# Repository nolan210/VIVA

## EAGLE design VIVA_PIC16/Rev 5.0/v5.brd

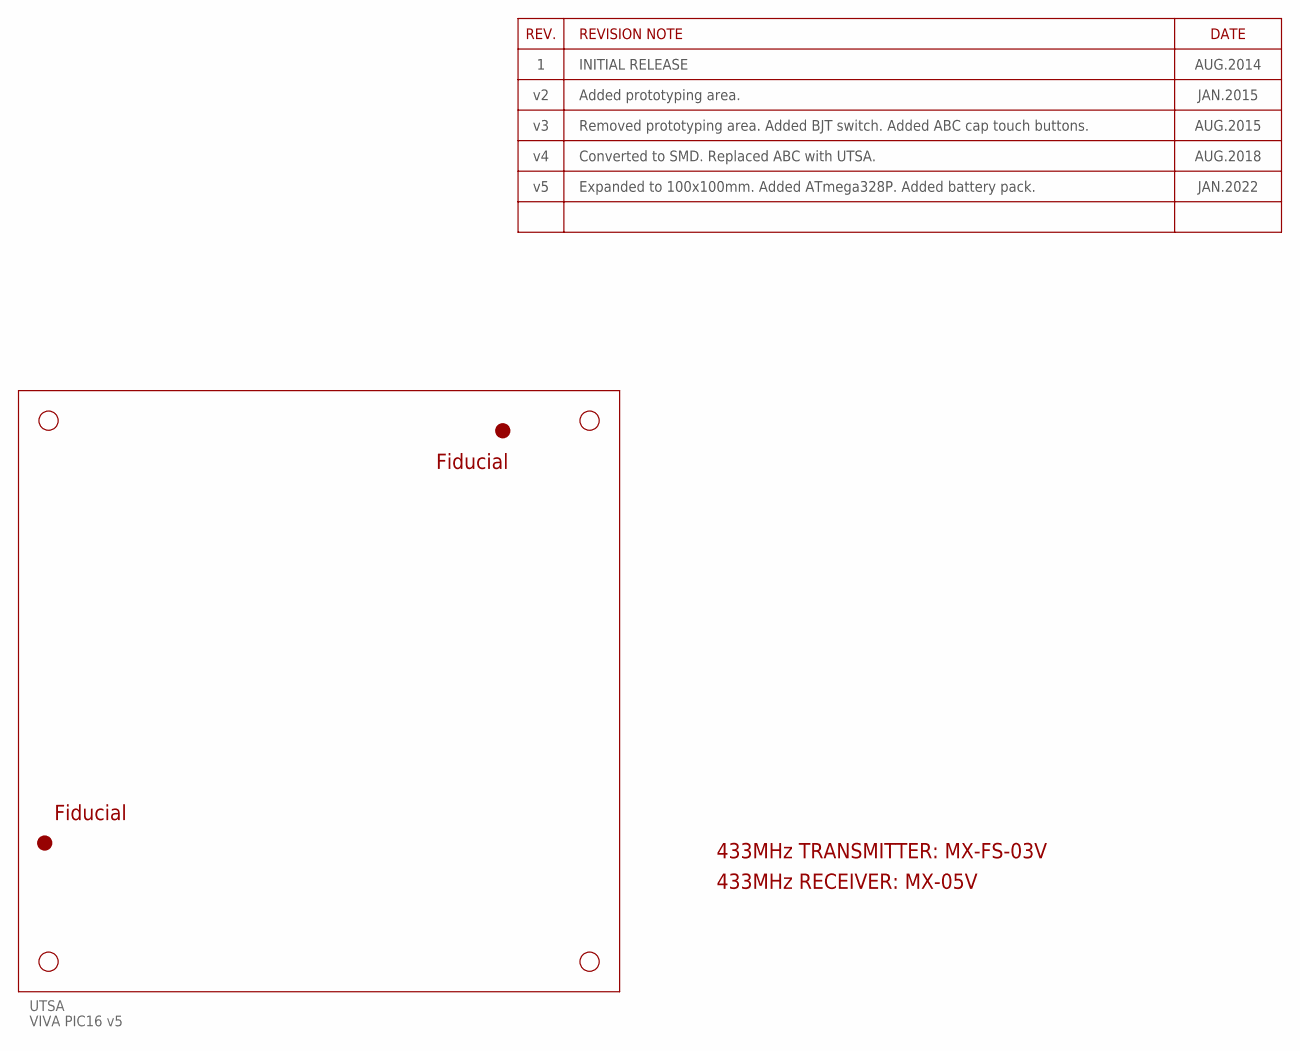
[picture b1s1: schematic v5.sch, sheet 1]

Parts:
FIDUCIAL1, FIDUCIAL2: FIDUCIAL
UTSA: VIVA PIC16 v5; PCB_100X100

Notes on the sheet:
Fiducial
433MHz TRANSMITTER: MX-FS-03V
433MHz RECEIVER: MX-05V

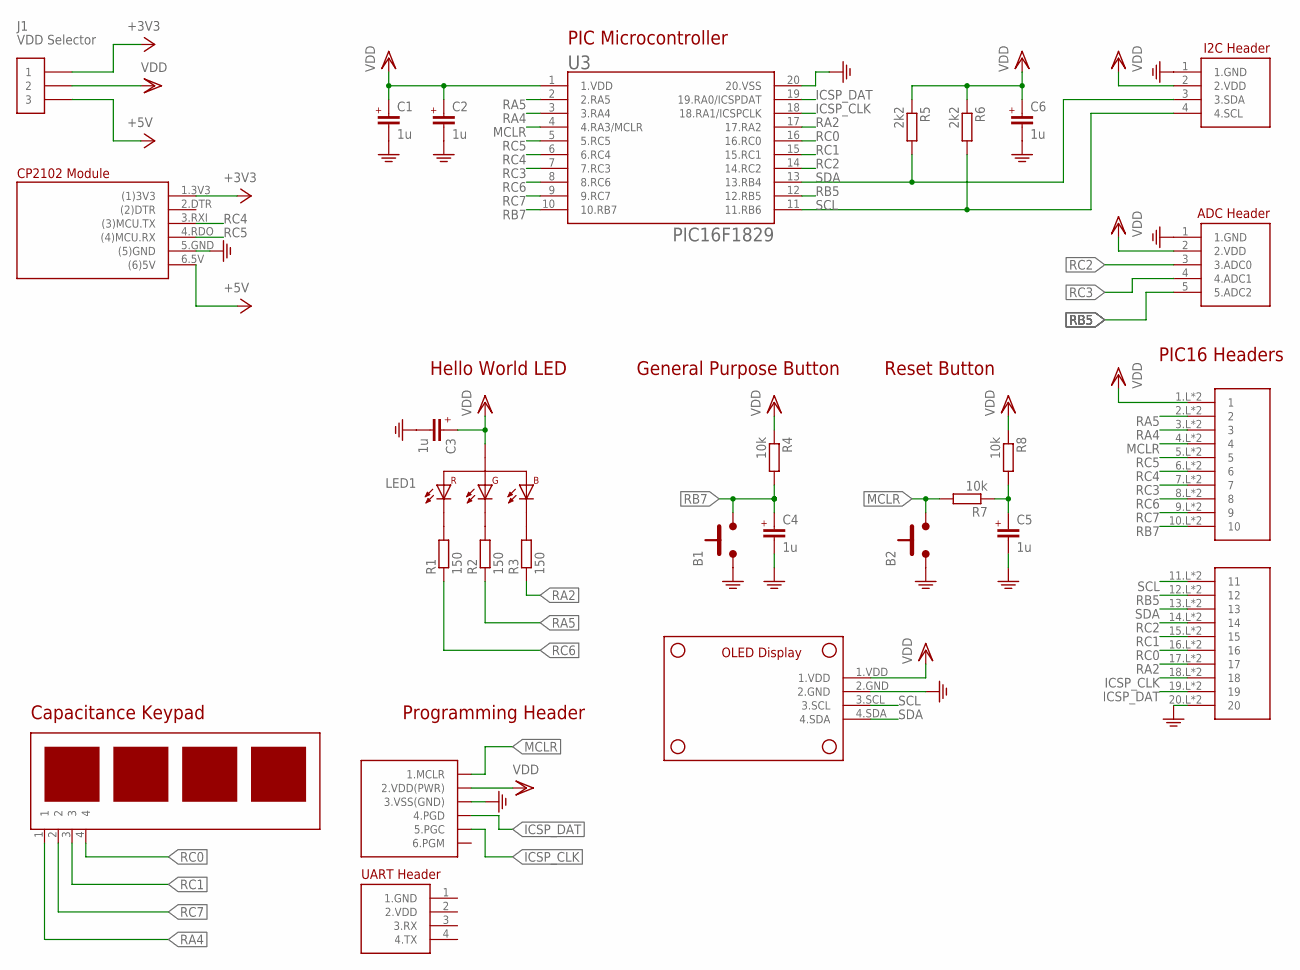
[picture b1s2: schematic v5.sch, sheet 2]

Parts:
B1, B2: PUSHBUTTON6X6MM; 6X6MM
C1, C2, C3, C4, C5, C6: 1u; C0805
J1: VDD Selector; PINS_3
J4: PICKIT3
J5: VIVA-HEADER-ADC-PIC16
LED1: LED_RGBLTST-C19FD1WT; 0805_RGB
R1, R2, R3: 150; R0805
R4, R7, R8: 10k; R0805
R5, R6: 2k2; R0805
U1: VIVA_UTSA-KEYPADV5; VIVA_UTSA-KEYPAD-V5
U2: VIVA_USB-TTL; VIVA_USB_TTL_SUBTEXT
U3: PIC16F1829; SOP20-NEW
U4: VIVA-HEADER-I2C-RA
U5: VIVA_PIC16BOARD; VIVA_PIC16
U$2: VIVA-HEADER-UART-XS; PINS_4
U$3: VIVA_OLED; VIVA_OLED-I2C

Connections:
+3V3: J1.1, U2.1.3V3 ((1)3V3); also elsewhere on the board
+5V: J1.3, U2.6.5V ((6)5V); also elsewhere on the board
GND: B1.1.A (1), B1.2.A (1), B2.1.A (1), B2.2.A (1), C1.1 (-), C2.1 (-), C3.1 (-), C4.1 (-), C5.1 (-), C6.1 (-), J4.3 (3.VSS(GND)), J5.1 (1.GND), U2.5.GND ((5)GND), U3.20 (20.VSS), U4.1 (1.GND), U5.20.L (20), U5.20.R (20), U$3.2.GND; also elsewhere on the board
ICSP_CLK: J4.5 (5.PGC), U3.18 (18.RA1/ICSPCLK), U5.18.L (18), U5.18.R (18)
ICSP_DAT: J4.4 (4.PGD), U3.19 (19.RA0/ICSPDAT), U5.19.L (19), U5.19.R (19)
MCLR: B2.3.B (2), B2.4.B (2), J4.1 (1.MCLR), R7.2, U3.4 (4.RA3/MCLR), U5.4.L (4), U5.4.R (4)
MCLR_CAP: C5.2 (+), R7.1, R8.2
unnamed: LED1.2 (1.R-), R1.2
unnamed: LED1.3 (2.G-), R2.2
unnamed: LED1.1 (4.B-), R3.2
RA2: R3.1, U3.17 (17.RA2), U5.17.L (17), U5.17.R (17)
RA4: U1.1, U3.3 (3.RA4), U5.3.L (3), U5.3.R (3)
RA5: R2.1, U3.2 (2.RA5), U5.2.L (2), U5.2.R (2)
RB5: J5.5 (5.ADC2), U3.12 (12.RB5), U5.12.L (12), U5.12.R (12)
RB7: B1.3.B (2), B1.4.B (2), C4.2 (+), R4.2, U3.10 (10.RB7), U5.10.L (10), U5.10.R (10)
RC0: U1.4, U3.16 (16.RC0), U5.16.L (16), U5.16.R (16)
RC1: U1.3, U3.15 (15.RC1), U5.15.L (15), U5.15.R (15)
RC2: J5.3 (3.ADC0), U3.14 (14.RC2), U5.14.L (14), U5.14.R (14)
RC3: J5.4 (4.ADC1), U3.7 (7.RC3), U5.7.L (7), U5.7.R (7)
RC4: U2.3.RXI ((3)MCU.TX), U3.6 (6.RC4), U5.6.L (6), U5.6.R (6)
RC5: U2.4.RDO ((4)MCU.RX), U3.5 (5.RC5), U5.5.L (5), U5.5.R (5)
RC6: R1.1, U3.8 (8.RC6), U5.8.L (8), U5.8.R (8)
RC7: U1.2, U3.9 (9.RC7), U5.9.L (9), U5.9.R (9)
SCL: R6.2, U3.11 (11.RB6), U4.4 (4.SCL), U5.11.L (11), U5.11.R (11), U$3.3.SCL; also elsewhere on the board
SDA: R5.2, U3.13 (13.RB4), U4.3 (3.SDA), U5.13.L (13), U5.13.R (13), U$3.4.SDA; also elsewhere on the board
VDD: C1.2 (+), C2.2 (+), C3.2 (+), C6.2 (+), J1.2, J4.2 (2.VDD(PWR)), J5.2 (2.VDD), LED1.4 (3.+), R4.1, R5.1, R6.1, R8.1, U3.1 (1.VDD), U4.2 (2.VDD), U5.1.L (1), U5.1.R (1), U$3.1.VDD; also elsewhere on the board

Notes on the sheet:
General Purpose Button
Hello World LED
PIC Microcontroller
Capacitance Keypad
Reset Button
Programming Header
PIC16 Headers

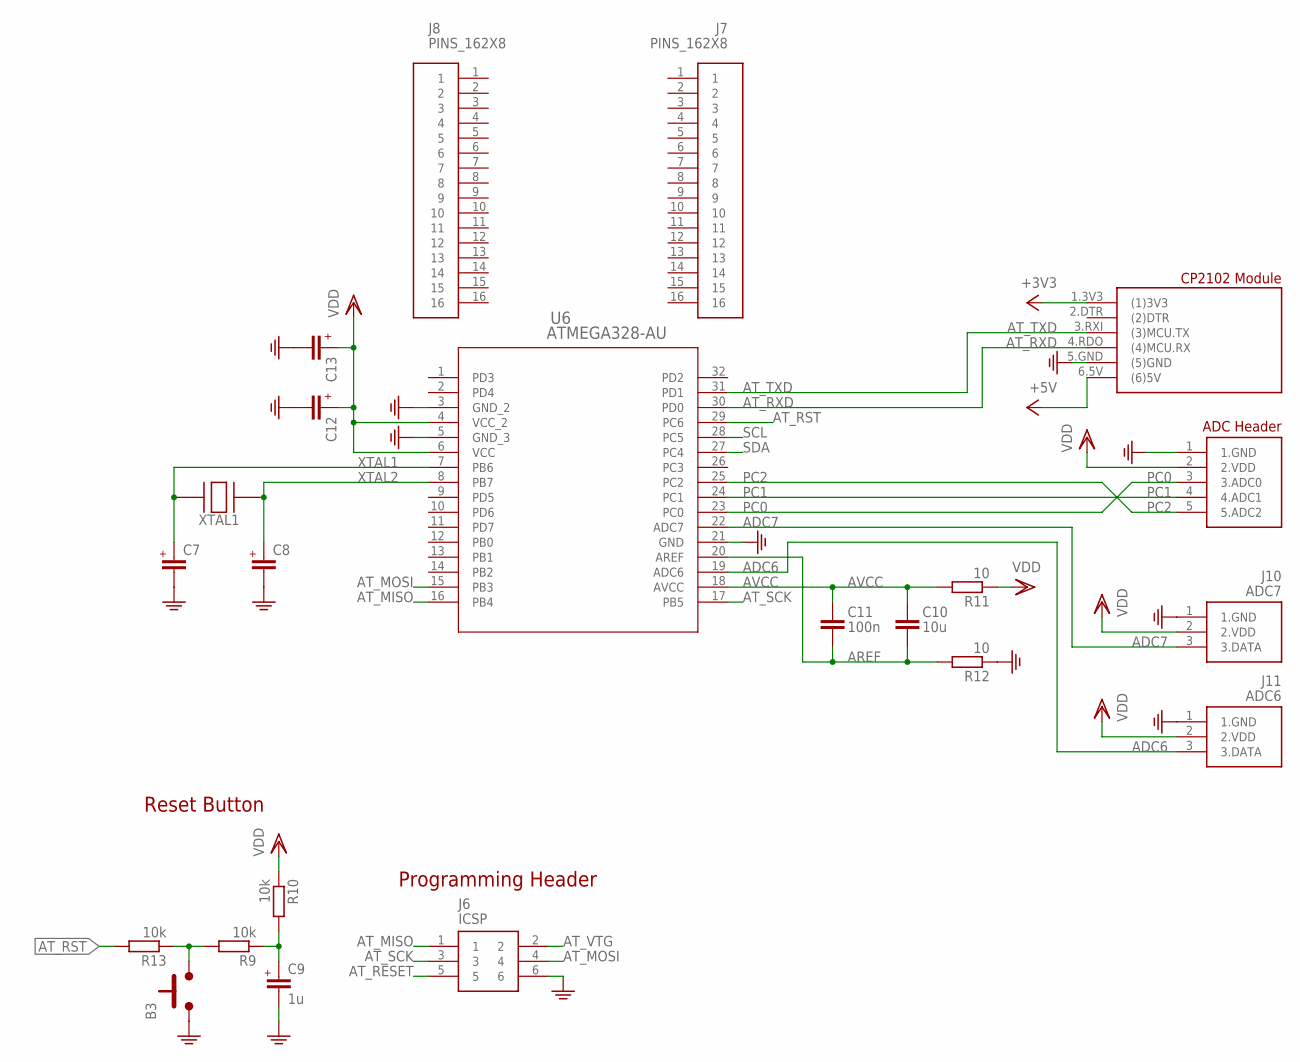
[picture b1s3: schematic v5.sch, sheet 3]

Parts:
B3: PUSHBUTTON6X6MM; 6X6MM
C7, C8, C12, C13: C0805
C9: 1u; C0805
C10: 10u; C0805
C11: 100n; C0805
J6: ICSP; PINS_6-2X3
J7, J8: PINS_162X8; PINS16_2X8
J9: VIVA-HEADER-ADC-PIC16
J10: ADC7; VIVA-HEADER-GPIO-RA-1
J11: ADC6; VIVA-HEADER-GPIO-RA-1
R9, R10, R13: 10k; R0805
R11, R12: 10; R0805
U6: ATMEGA328-AU; 32A_ATM
U7: VIVA_USB-TTL; VIVA_USB_TTL_SUBTEXT
XTAL1: CRYSTAL-SMD; HC49S-SMD

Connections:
+3V3: U7.1.3V3 ((1)3V3); also elsewhere on the board
+5V: U7.6.5V ((6)5V); also elsewhere on the board
ADC6: J11.3 (3.DATA), U6.19 (ADC6)
ADC7: J10.3 (3.DATA), U6.22 (ADC7)
AREF: C10.2, C11.2, R12.2, U6.20 (AREF)
AT_MISO: J6.1, U6.16 (PB4)
AT_MOSI: J6.4, U6.15 (PB3)
AT_RESET: J6.5
AT_RST: R13.2, U6.29 (PC6)
AT_RST_BTN: B3.3.B (2), B3.4.B (2), R9.2, R13.1
AT_RST_CAP: C9.2 (+), R9.1, R10.2
AT_RXD: U6.30 (PD0), U7.4.RDO ((4)MCU.RX)
AT_SCK: J6.3, U6.17 (PB5)
AT_TXD: U6.31 (PD1), U7.3.RXI ((3)MCU.TX)
AT_VTG: J6.2
AVCC: C10.1, C11.1, R11.2, U6.18 (AVCC)
GND: B3.1.A (1), B3.2.A (1), C7.1 (-), C8.1 (-), C9.1 (-), C12.1 (-), C13.1 (-), J6.6, J9.1 (1.GND), J10.1 (1.GND), J11.1 (1.GND), R12.1, U6.3 (GND_2), U6.5 (GND_3), U6.21 (GND), U7.5.GND ((5)GND); also elsewhere on the board
PC0: J9.3 (3.ADC0), U6.23 (PC0)
PC1: J9.4 (4.ADC1), U6.24 (PC1)
PC2: J9.5 (5.ADC2), U6.25 (PC2)
SCL: U6.28 (PC5); also elsewhere on the board
SDA: U6.27 (PC4); also elsewhere on the board
VDD: C12.2 (+), C13.2 (+), J9.2 (2.VDD), J10.2 (2.VDD), J11.2 (2.VDD), R10.1, R11.1, U6.4 (VCC_2), U6.6 (VCC); also elsewhere on the board
XTAL1: C7.2 (+), U6.7 (PB6), XTAL1.2, XTAL1.4 (2)
XTAL2: C8.2 (+), U6.8 (PB7), XTAL1.1, XTAL1.3 (1)

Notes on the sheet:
Reset Button
Programming Header

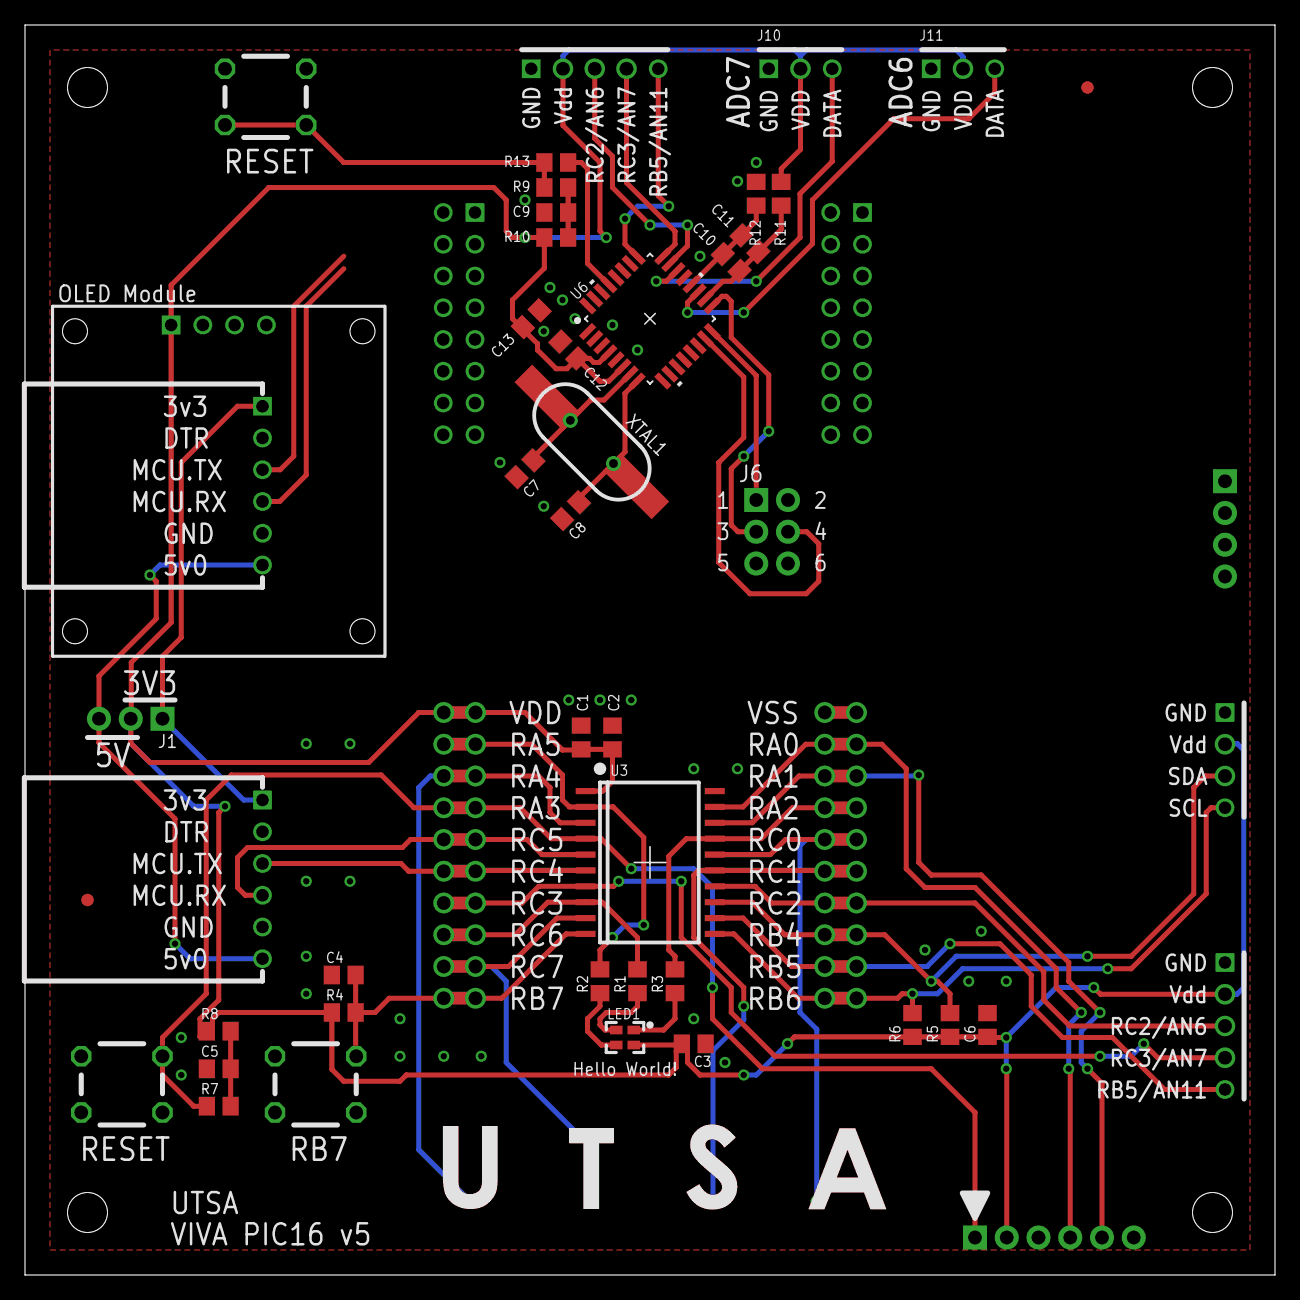
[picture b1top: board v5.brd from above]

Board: 4 copper layers, 100.0 x 100.0 mm, 52 parts (0 on the bottom side), 43 nets.

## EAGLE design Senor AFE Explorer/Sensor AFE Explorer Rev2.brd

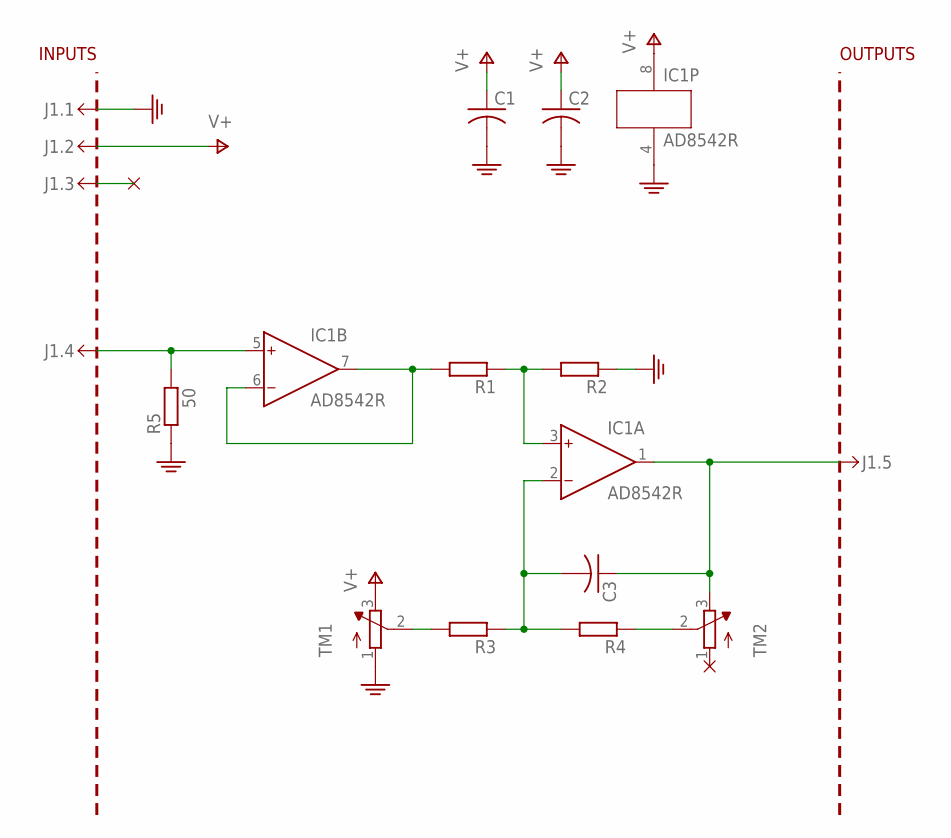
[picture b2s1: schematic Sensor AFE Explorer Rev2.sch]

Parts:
C1, C2, C3: C-USC0805; C0805
IC1: AD8542R; SO8
J1.: MINIPCB_5P50X50; MINIPCB_50X50MM; PART_NUMBER AFE Explorer
R1, R2, R3, R4: RESISTORSMD; R0805
R5: 50; R0805
TM1, TM2: TRIMPOT3386; TRIM-3386

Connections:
GND: C1.2, C2.2, IC1.4 (V-), J1..1, R2.1, R5.1, TM1.1 (A)
unnamed: IC1.5 (IN+), J1..4, R5.2
unnamed: IC1.6 (IN-), IC1.7 (OUT), R1.2
unnamed: IC1.3 (IN+), R1.1, R2.2
unnamed: C3.2, IC1.2 (IN-), R3.1, R4.2
unnamed: R3.2, TM1.2 (S)
unnamed: R4.1, TM2.2 (S)
unnamed: C3.1, IC1.1 (OUT), J1..5, TM2.3 (E)
V+: C1.1, C2.1, IC1.8 (V+), J1..2, TM1.3 (E)

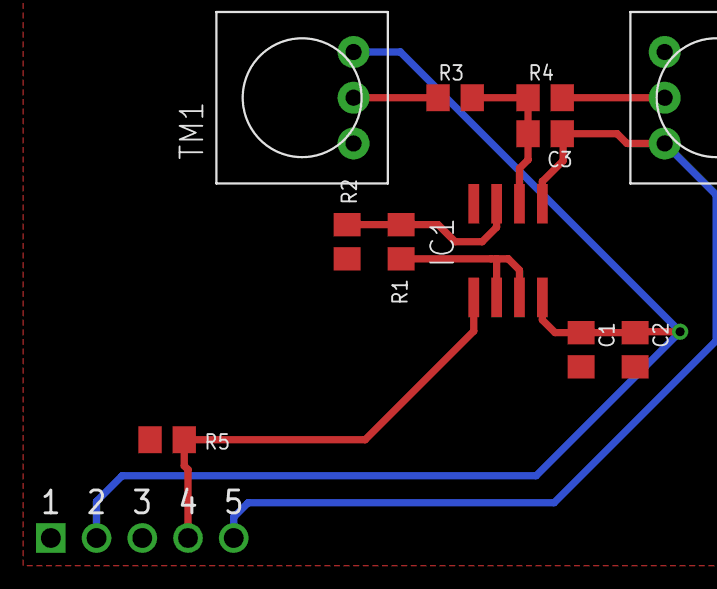
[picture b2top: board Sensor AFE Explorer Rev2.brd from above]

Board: 2 copper layers, 12 parts (0 on the bottom side), 9 nets.

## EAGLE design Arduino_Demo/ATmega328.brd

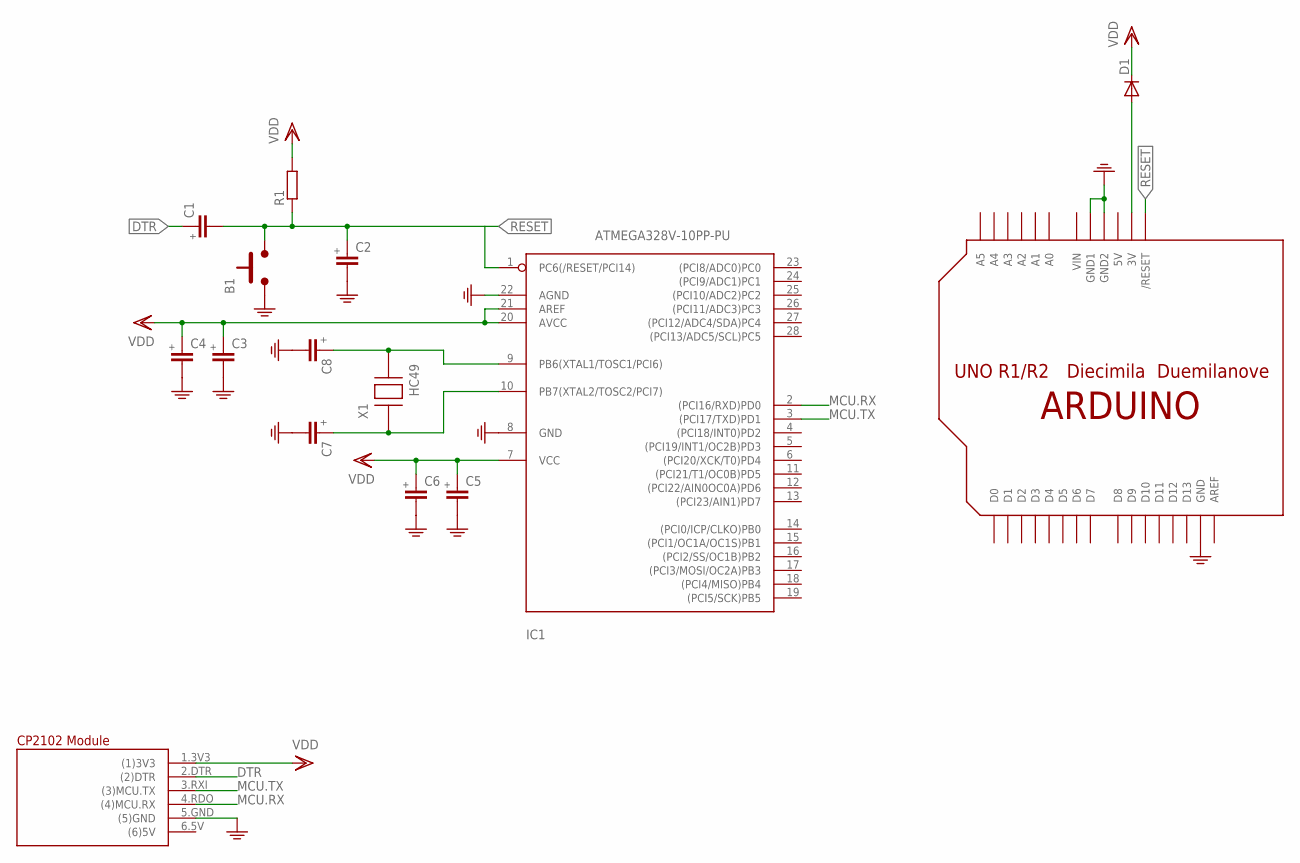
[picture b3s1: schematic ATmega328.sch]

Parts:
B1: PUSHBUTTON6X6MM; 6X6MM
C1, C2, C3, C4, C5, C6, C7, C8: C-EUC0805; C0805
D1: DIODE-SOD123; SOD123
IC1: ATMEGA328V-10PP-PU; DIL28-3
R1: R-EU_R0805; R0805
U$2: ARDUINOUNO; ARDUINO
U$3: VIVA_USB-TTLTEXT; VIVA_USB-TTL
X1: HC49; HC49S

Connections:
5V: U$2.5V
DTR: C1.1, U$3.2.DTR ((2)DTR)
GND: B1.1.A (1), B1.2.A (1), C2.2, C3.2, C4.2, C5.2, C6.2, C7.2, C8.2, IC1.8 (GND), IC1.22 (AGND), U$2.GND, U$2.GND1, U$2.GND2, U$3.5.GND ((5)GND)
MCU.RX: IC1.2 ((PCI16/RXD)PD0), U$3.4.RDO ((4)MCU.RX)
MCU.TX: IC1.3 ((PCI17/TXD)PD1), U$3.3.RXI ((3)MCU.TX)
unnamed: D1.A, U$2.3V
unnamed: C8.1, IC1.9 (PB6(XTAL1/TOSC1/PCI6)), X1.P$2
unnamed: C7.1, IC1.10 (PB7(XTAL2/TOSC2/PCI7)), X1.P$1
RESET: B1.3.B (2), B1.4.B (2), C1.2, C2.1, IC1.1 (PC6(/RESET/PCI14)), R1.1, U$2.RESET (/RESET)
VDD: C3.1, C4.1, C5.1, C6.1, D1.C, IC1.7 (VCC), IC1.20 (AVCC), IC1.21 (AREF), R1.2, U$3.1.3V3 ((1)3V3)
VIN: U$2.VIN

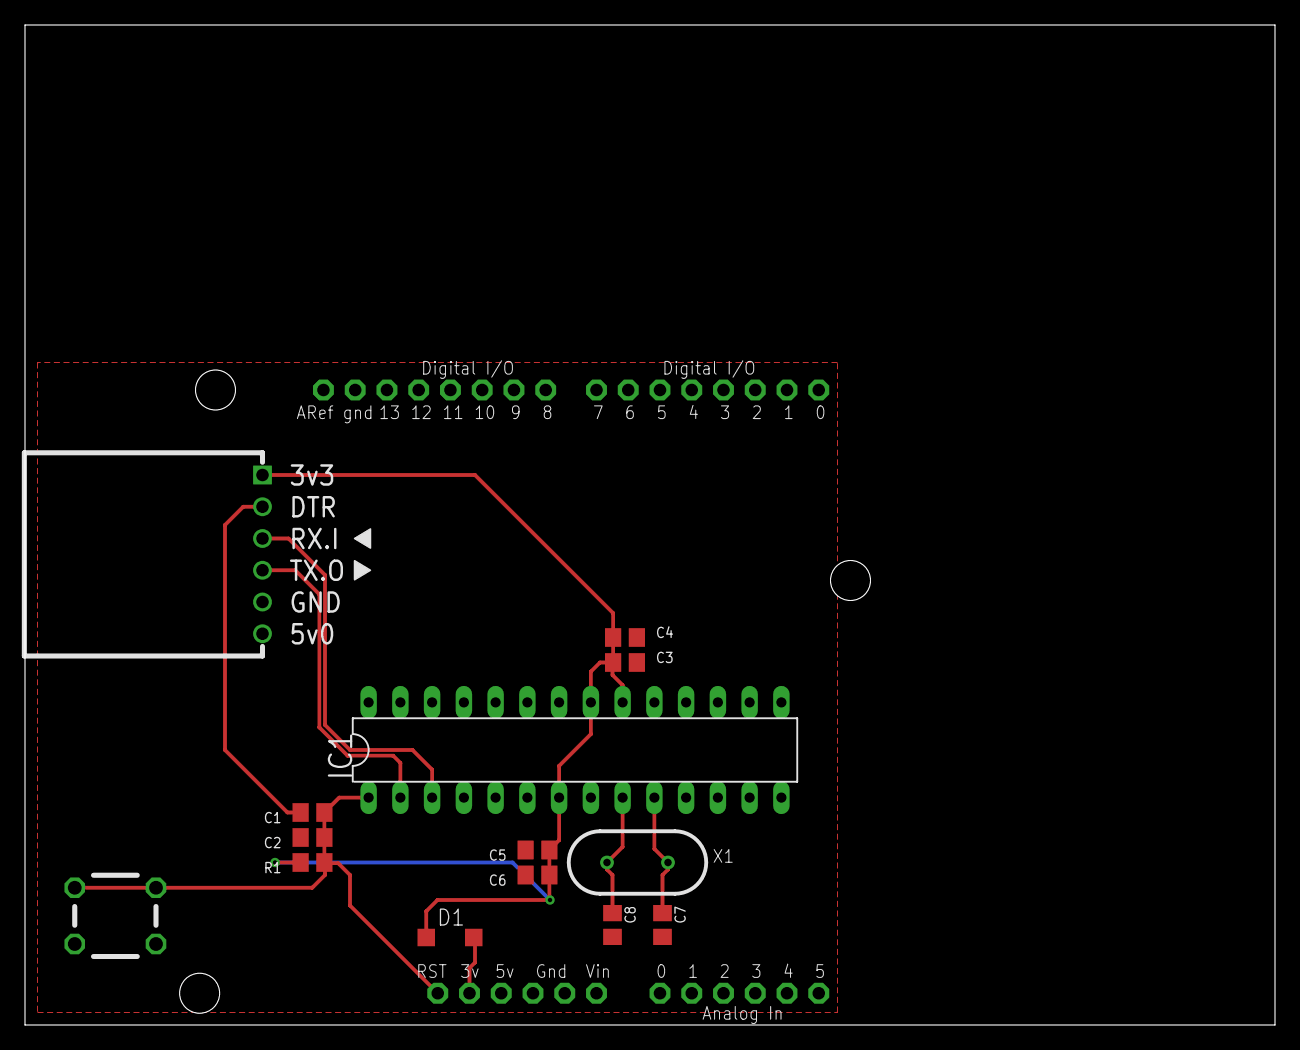
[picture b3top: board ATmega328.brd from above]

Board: 2 copper layers, 100.0 x 80.0 mm, 15 parts (0 on the bottom side), 9 nets.

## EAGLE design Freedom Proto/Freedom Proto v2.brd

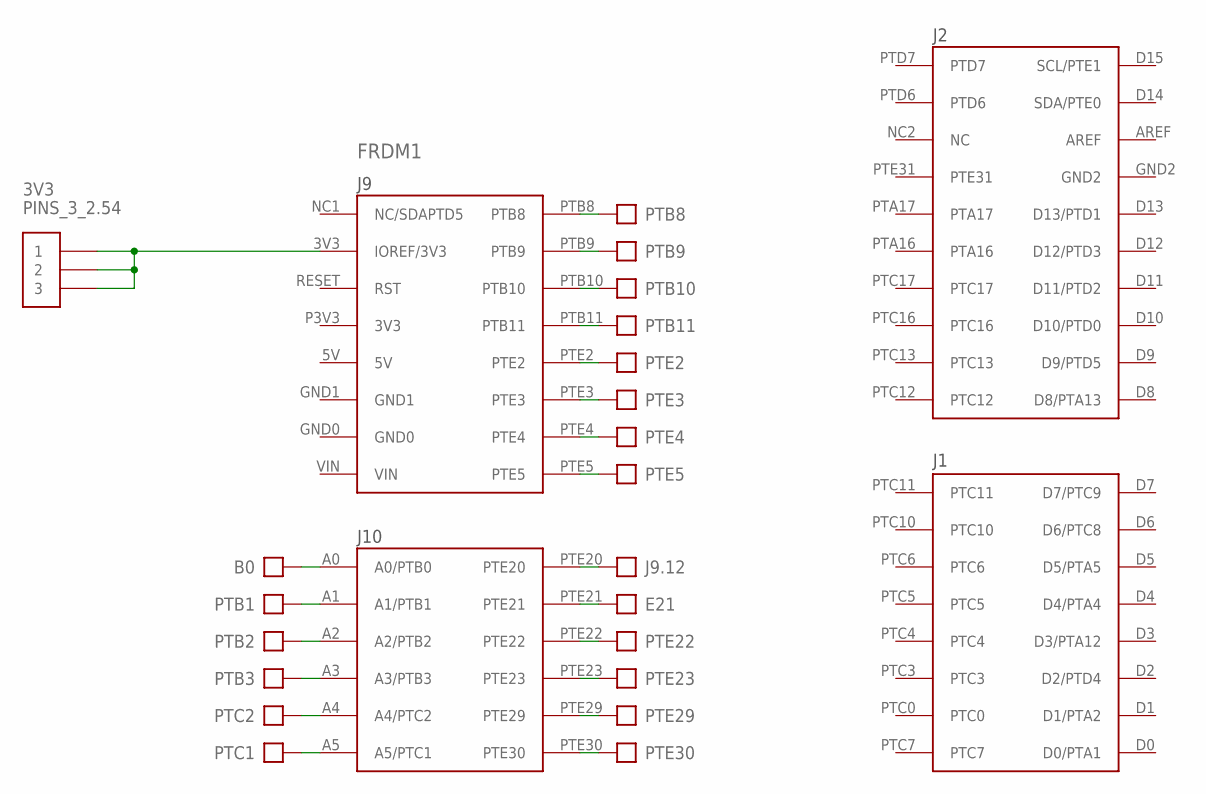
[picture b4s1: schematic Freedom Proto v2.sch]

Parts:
3V3: PINS_3_2.54; PINS_3
B0: PINS_1; PINS_1_TEXT
E21: PINS_1; PINS_1_TEXT
FRDM1: FRDM-KL25ZNORMAL; FRDM_KL25Z_NORMAL
J9.12: PINS_1; PINS_1_TEXT
PTB1, PTB2, PTB3, PTB8, PTB9, PTB10, PTB11: PINS_1; PINS_1_TEXT
PTC1, PTC2: PINS_1; PINS_1_TEXT
PTE2, PTE3, PTE4, PTE5, PTE22, PTE23, PTE29, PTE30: PINS_1; PINS_1_TEXT

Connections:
unnamed: B0.1, FRDM1.A0 (A0/PTB0)
unnamed: FRDM1.A1 (A1/PTB1), PTB1.1
unnamed: FRDM1.A2 (A2/PTB2), PTB2.1
unnamed: FRDM1.A3 (A3/PTB3), PTB3.1
unnamed: FRDM1.A5 (A5/PTC1), PTC1.1
unnamed: FRDM1.PTE20, J9.12.1
unnamed: E21.1, FRDM1.PTE21
unnamed: FRDM1.PTE22, PTE22.1
unnamed: FRDM1.PTE23, PTE23.1
unnamed: FRDM1.PTE29, PTE29.1
unnamed: FRDM1.PTE30, PTE30.1
unnamed: FRDM1.A4 (A4/PTC2), PTC2.1
unnamed: 3V3.1, 3V3.2, 3V3.3, FRDM1.3V3 (IOREF/3V3)
unnamed: FRDM1.PTB8, PTB8.1
unnamed: FRDM1.PTB9, PTB9.1
unnamed: FRDM1.PTB10, PTB10.1
unnamed: FRDM1.PTB11, PTB11.1
unnamed: FRDM1.PTE2, PTE2.1
unnamed: FRDM1.PTE3, PTE3.1
unnamed: FRDM1.PTE4, PTE4.1
unnamed: FRDM1.PTE5, PTE5.1

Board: 2 copper layers, 22 parts (0 on the bottom side), 21 nets, no tracks yet.

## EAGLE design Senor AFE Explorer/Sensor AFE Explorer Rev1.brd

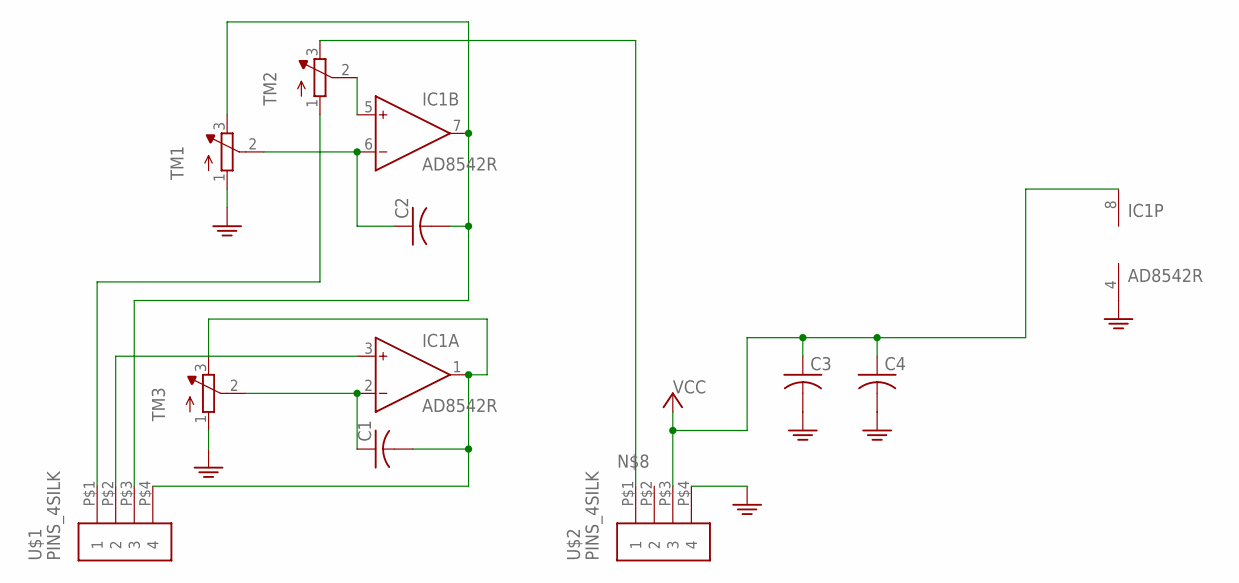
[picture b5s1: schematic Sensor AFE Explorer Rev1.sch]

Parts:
C1, C2, C3, C4: C-USC0805; C0805
IC1: AD8542R; SO8
TM1, TM2, TM3: TRIMPOT3386; TRIM-3386
U$1, U$2: PINS_4SILK; PCB_4

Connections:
GND: C3.2, C4.2, IC1.4 (V-), TM1.1 (A), TM3.1 (A), U$2.P$4 (4)
unnamed: C2.1, IC1.6 (IN-), TM1.2 (S)
unnamed: C2.2, IC1.7 (OUT), TM1.3 (E), U$1.P$3 (3)
unnamed: C1.1, IC1.2 (IN-), TM3.2 (S)
unnamed: C1.2, IC1.1 (OUT), TM3.3 (E), U$1.P$4 (4)
unnamed: IC1.3 (IN+), U$1.P$2 (2)
unnamed: TM2.1 (A), U$1.P$1 (1)
unnamed: IC1.5 (IN+), TM2.2 (S)
unnamed: TM2.3 (E), U$2.P$1 (1)
VCC: C3.1, C4.1, IC1.8 (V+), U$2.P$3 (3)

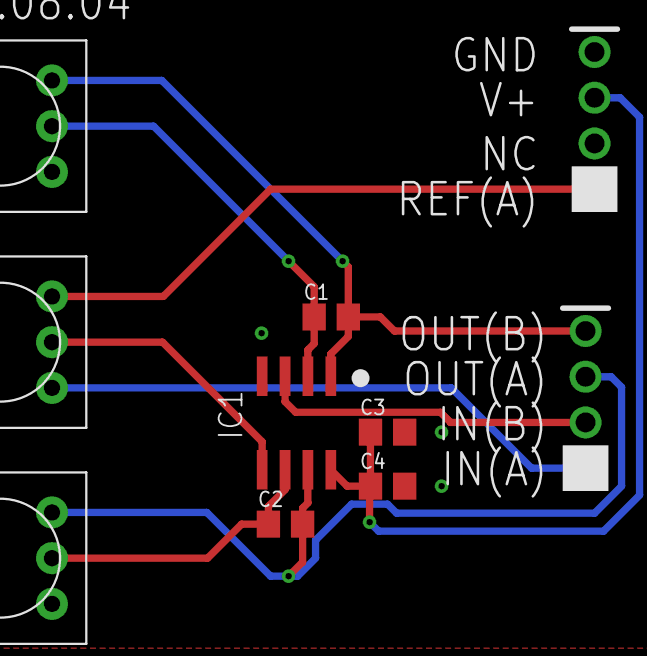
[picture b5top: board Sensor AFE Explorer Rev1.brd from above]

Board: 2 copper layers, 10 parts (0 on the bottom side), 10 nets.

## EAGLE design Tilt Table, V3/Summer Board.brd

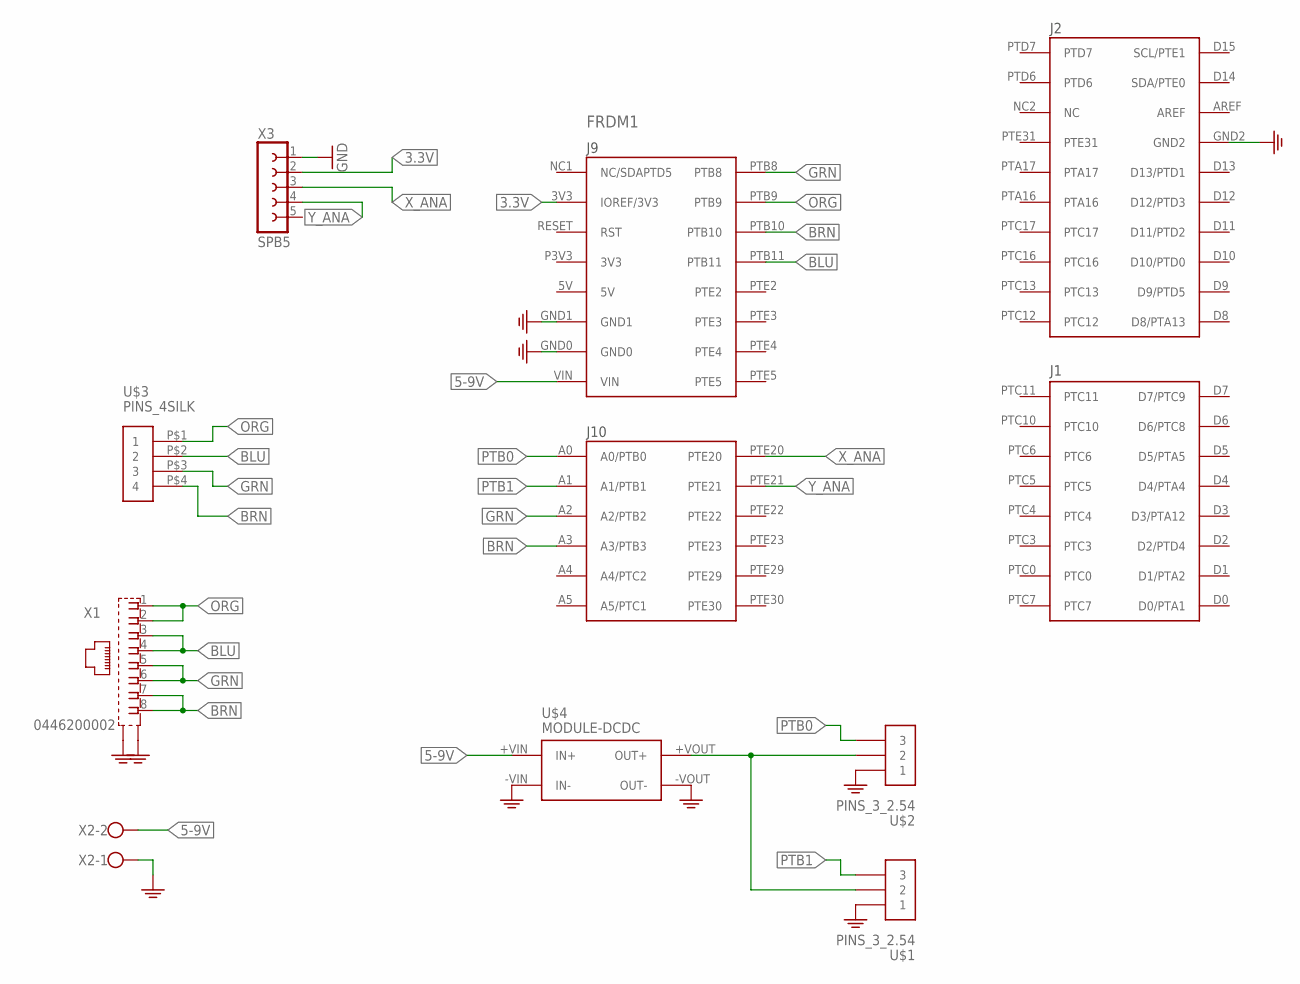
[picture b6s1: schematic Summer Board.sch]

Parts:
FRDM1: FRDM-KL25ZNORMAL; FRDM_KL25Z_NORMAL
U$1, U$2: PINS_3_2.54; PINS_3
U$3: PINS_4SILK; PCB_4
U$4: MODULE-DCDC; DCDC_CONVERTER_MH
X1: 0446200002
X2: W237-102
X3: SPB5

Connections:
3.3V: FRDM1.3V3 (IOREF/3V3), X3.2
5-9V: FRDM1.VIN, U$4.+VIN (IN+), X2.2
BLU: FRDM1.PTB11, U$3.P$2 (2), X1.3, X1.4
BRN: FRDM1.A3 (A3/PTB3), FRDM1.PTB10, U$3.P$4 (4), X1.7, X1.8
GND: FRDM1.GND0, FRDM1.GND1, FRDM1.GND2, U$1.1, U$2.1, U$4.-VIN (IN-), U$4.-VOUT (OUT-), X1.S@1 (S1), X1.S@2 (S2), X2.1, X3.1
GRN: FRDM1.A2 (A2/PTB2), FRDM1.PTB8, U$3.P$3 (3), X1.5, X1.6
unnamed: U$1.2, U$2.2, U$4.+VOUT (OUT+)
ORG: FRDM1.PTB9, U$3.P$1 (1), X1.1, X1.2
PTB0: FRDM1.A0 (A0/PTB0), U$2.3
PTB1: FRDM1.A1 (A1/PTB1), U$1.3
X_ANA: FRDM1.PTE20, X3.3
Y_ANA: FRDM1.PTE21, X3.4

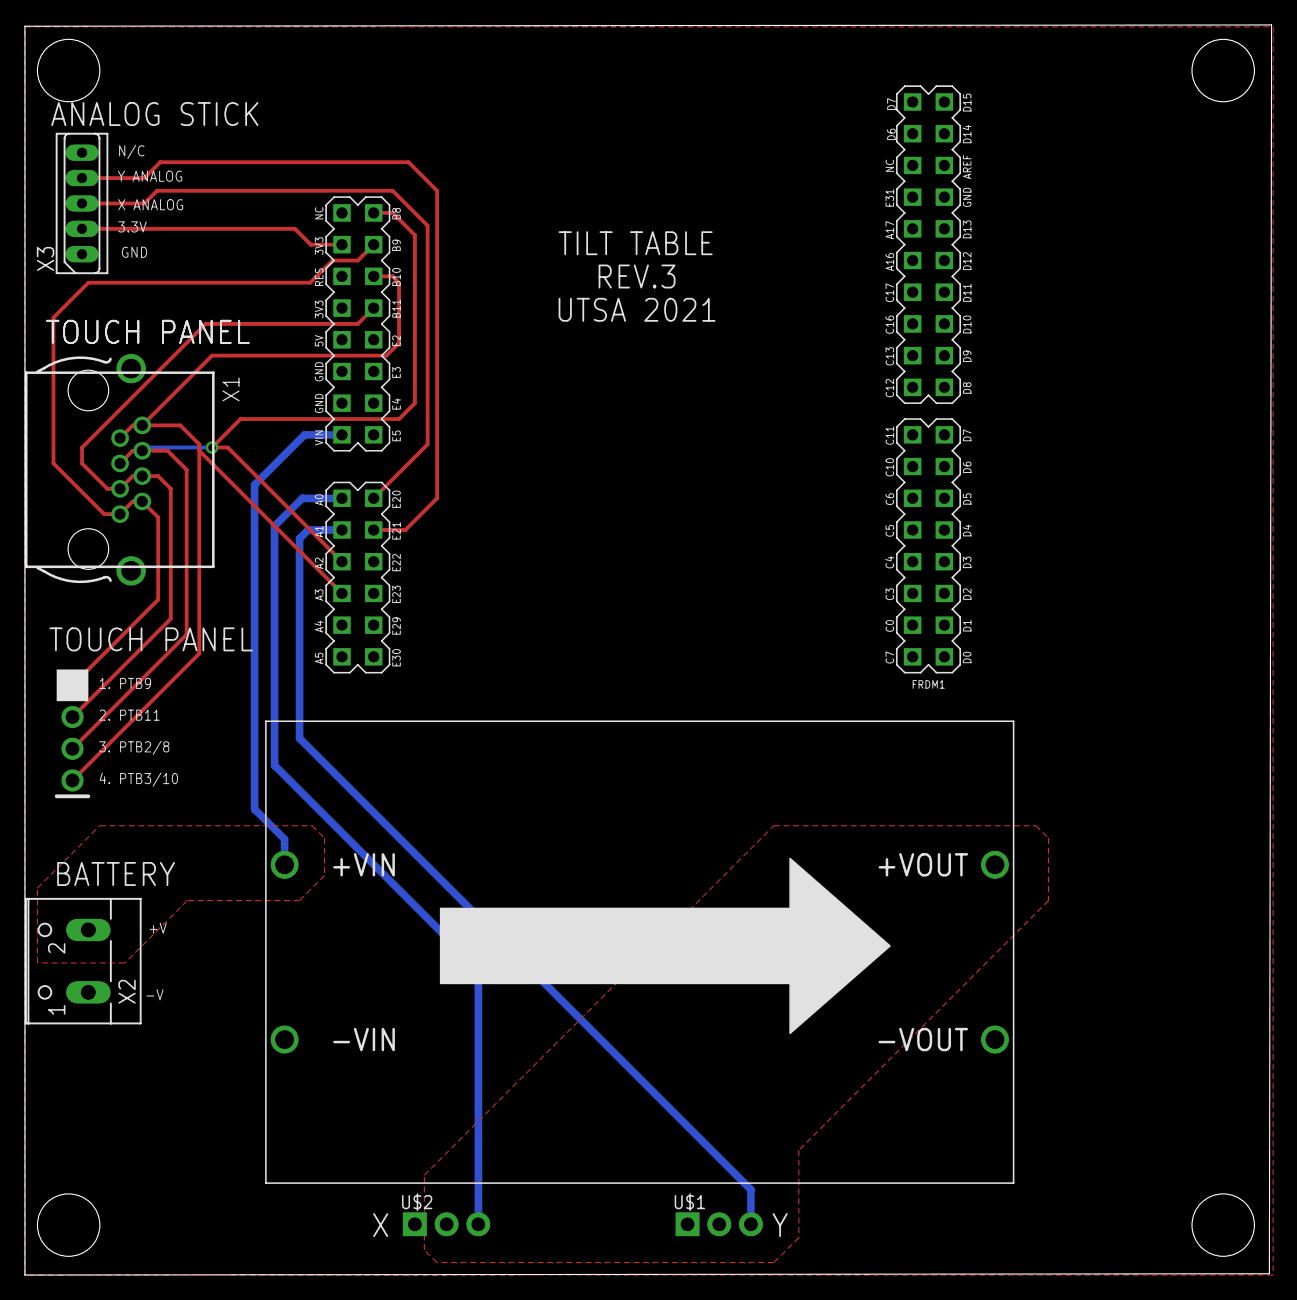
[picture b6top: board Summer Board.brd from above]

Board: 2 copper layers, 99.9 x 100.2 mm, 8 parts (0 on the bottom side), 12 nets.

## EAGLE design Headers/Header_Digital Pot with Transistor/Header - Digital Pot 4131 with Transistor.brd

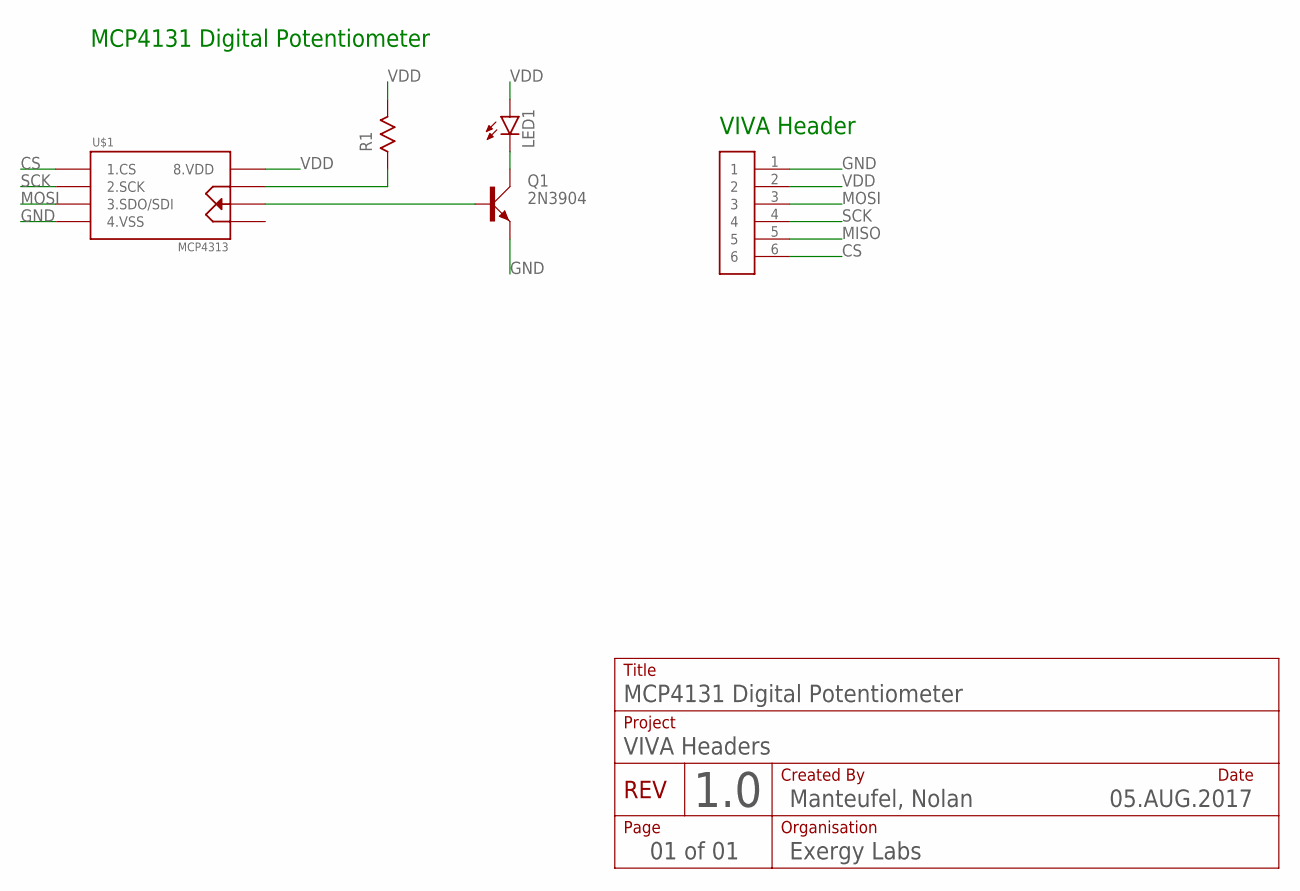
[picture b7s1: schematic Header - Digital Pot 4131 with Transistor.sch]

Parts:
LED1: LED5MM
Q1: 2N3904; TO92-EBC-OVAL
R1: R204-7; 0204/7
U$1: MCP4131; DIL08
U$2: PINS_6SQUARE; PINS_6

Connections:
CS: U$1.1 (1.CS), U$2.6
GND: Q1.E, U$1.4 (4.VSS), U$2.1
MISO: U$2.5
MOSI: U$1.3 (3.SDO/SDI), U$2.3
unnamed: LED1.K (C), Q1.C
unnamed: Q1.B, U$1.6 (6.P0W)
unnamed: R1.1, U$1.7 (7.P0B)
SCK: U$1.2 (2.SCK), U$2.4
VDD: LED1.A, R1.2, U$1.8 (8.VDD), U$2.2

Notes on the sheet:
VIVA Headers
REV
1.0
Created By
Organisation
Date
Manteufel, Nolan
05.AUG.2017
Page
01 of 01
Project
MCP4131 Digital Potentiometer
Title
Exergy Labs
VIVA Header

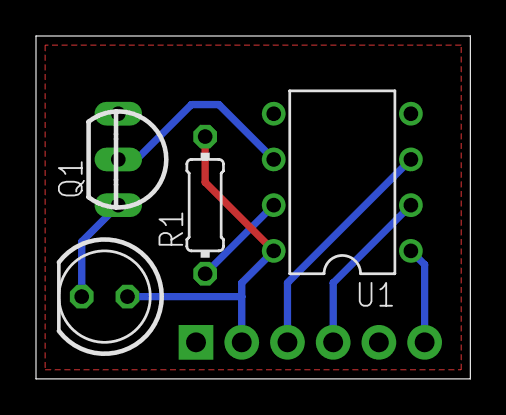
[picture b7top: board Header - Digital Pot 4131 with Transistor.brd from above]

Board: 2 copper layers, 24.1 x 19.1 mm, 5 parts (0 on the bottom side), 8 nets.

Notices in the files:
parts and their libraries:
COPYRIGHT: Copyright (C) 2021 Ultra Librarian. All rights reserved.
